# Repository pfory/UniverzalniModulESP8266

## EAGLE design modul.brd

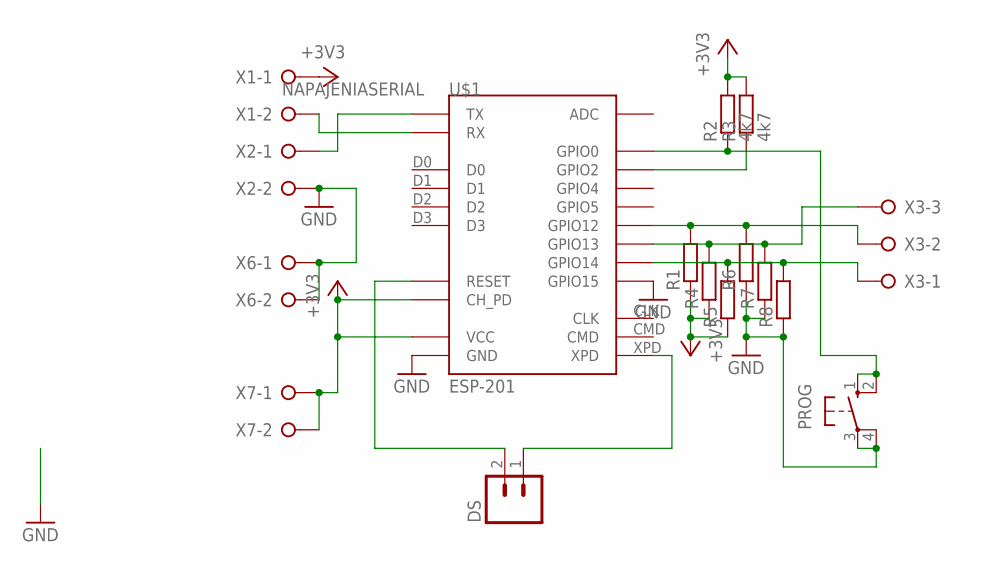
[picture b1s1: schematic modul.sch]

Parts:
DS: M02; 02P
PROG: 10-XX; B3F-10XX
R1, R4, R5, R6, R7, R8: R-EU_0207/10; 0207/10
R2, R3: 4k7; 0207/10
U$1: ESP-201
X1: NAPAJENIASERIAL; W237-132
X2, X6, X7: W237-02P; W237-132
X3: W237-03P; W237-133

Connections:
+3V3: R1.1, R2.2, R3.2, R4.1, R5.1, U$1.3V3 (VCC), U$1.3V3_2 (VCC), U$1.3V3_3 (VCC), U$1.CH_PD, X1.1, X7.1, X7.2
GND: PROG.3, PROG.4 (P1), R6.1, R7.1, R8.1, U$1.GND, U$1.GND_2 (GND), U$1.GND_3 (GND), U$1.GPIO15, X2.2, X6.1, X6.2
unnamed: U$1.TX, X2.1
unnamed: DS.2, U$1.RST (RESET)
unnamed: R1.2, R6.2, U$1.GPIO12, X3.2
unnamed: R4.2, R7.2, U$1.GPIO13, X3.3
unnamed: DS.1, U$1.XPD
unnamed: R5.2, R8.2, U$1.GPIO14, X3.1
unnamed: U$1.RX, X1.2
unnamed: PROG.1 (S), PROG.2 (S1), R2.1, U$1.GPIO0
unnamed: R3.1, U$1.GPIO2

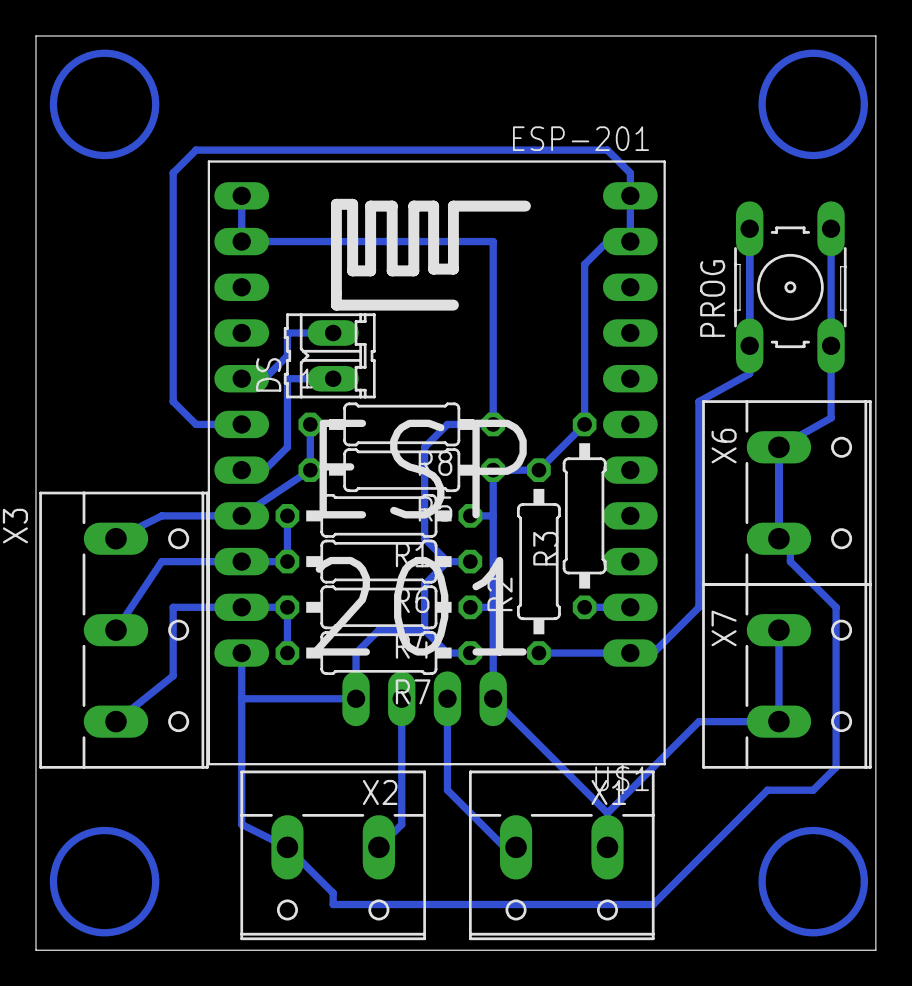
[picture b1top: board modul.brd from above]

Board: 2 copper layers, 46.7 x 50.8 mm, 16 parts (0 on the bottom side), 11 nets.
